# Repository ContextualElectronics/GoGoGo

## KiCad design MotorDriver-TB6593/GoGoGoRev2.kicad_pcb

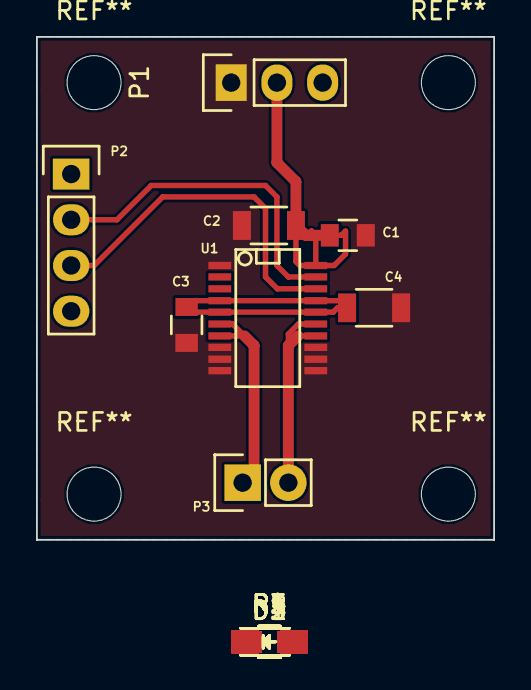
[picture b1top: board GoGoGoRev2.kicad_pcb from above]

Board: 2 copper layers, 25.4 x 27.9 mm, 17 parts (0 on the bottom side), 13 nets.

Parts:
C1, C3: .1U; C_0805
C2, C4: 10U; C_1206
D1, D2, D3, D4: LED; LED-0805
P1: CONN_01X03; Pin_Header_Straight_1x03
P2: CONN_01X04; Pin_Header_Straight_1x04
P3: CONN_01X02; Pin_Header_Straight_1x02
R1, R2, R3, R4: 1K; R_0805_HandSoldering
R5: 0; R_0805_HandSoldering
U1: TB6593FNG; SSOP-20

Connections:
/IN1: D3.2, P2.3, U1.18
/IN2: D4.2, P2.2, U1.19
/O1: P3.1, U1.6, U1.7
/O2: P3.2, U1.14, U1.15
/PWM: P2.1, U1.2
/STBY: P2.4, U1.3
/VCC: C1.1, C2.1, P1.2, R5.2, U1.20
/VM: C3.1, C4.1, D1.2, D2.2, P1.3, R5.1, U1.4, U1.5, U1.16, U1.17
GND: C1.2, C2.2, C3.2, C4.2, P1.1, R1.1, R2.1, R3.1, R4.1, U1.1, U1.8, U1.9, U1.10, U1.11, U1.12, U1.13
unnamed: D1.1, R1.2
unnamed: D2.1, R2.2
unnamed: D3.1, R3.2
unnamed: D4.1, R4.2

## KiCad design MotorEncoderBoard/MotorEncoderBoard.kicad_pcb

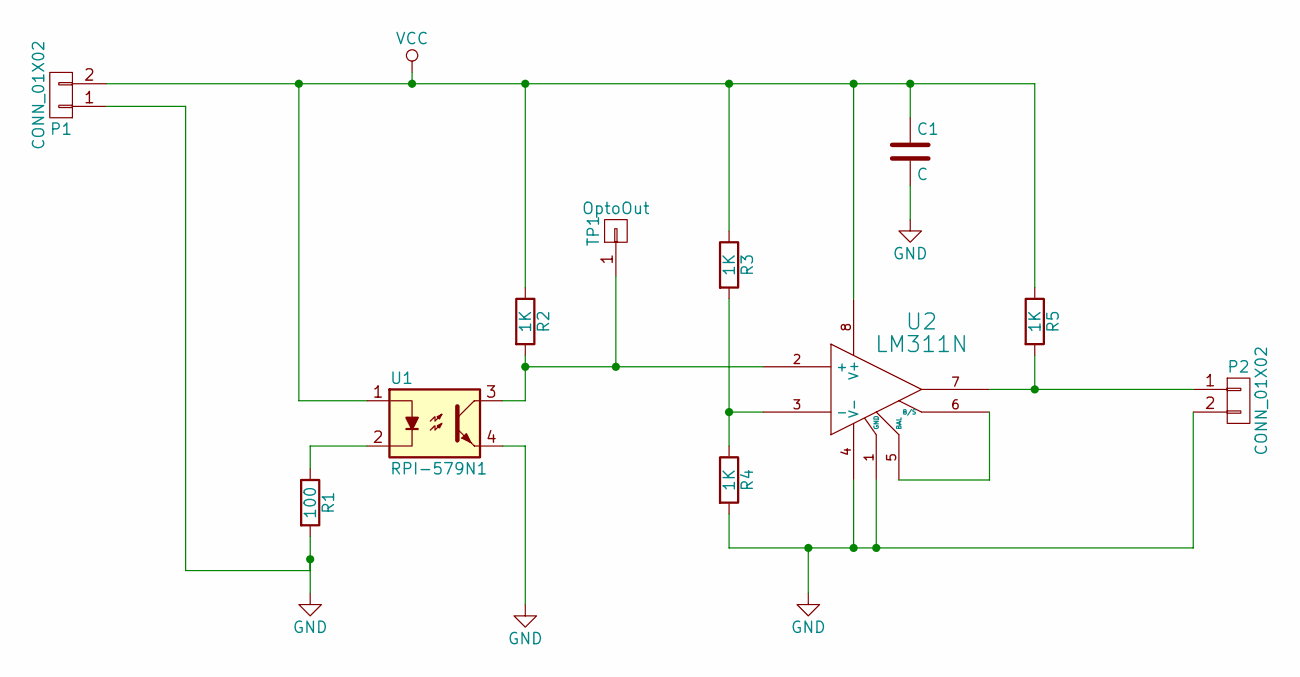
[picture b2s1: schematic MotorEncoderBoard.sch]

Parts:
C1: C; C_0805_HandSoldering
P1, P2: CONN_01X02; Pin_Header_Straight_1x02
R1: 100; R_0805_HandSoldering
R2, R3, R4, R5: 1K; R_0805_HandSoldering
TP1: OptoOut; Measurement_Point_Round-SMD-Pad_Big
U1: RPI-579N1
U2: LM311N; SOIC-8_3.9x4.9mm_Pitch1.27mm

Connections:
GND: C1.2, P1.1, P2.2, R1.2, R4.2, U1.4, U2.1 (GND), U2.4 (V-)
unnamed: P2.1, R5.2, U2.7
unnamed: R1.1, U1.2
unnamed: R2.2, TP1.1, U1.3, U2.2 (+)
unnamed: R3.2, R4.1, U2.3 (-)
unnamed: U2.5 (BAL), U2.6 (B/S)
VCC: C1.1, P1.2, R2.1, R3.1, R5.1, U1.1, U2.8 (V+)

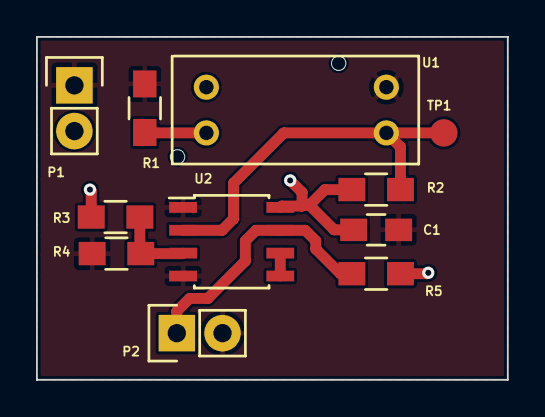
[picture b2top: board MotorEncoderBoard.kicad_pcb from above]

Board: 2 copper layers, 26.2 x 19.0 mm, 11 parts (0 on the bottom side), 7 nets.

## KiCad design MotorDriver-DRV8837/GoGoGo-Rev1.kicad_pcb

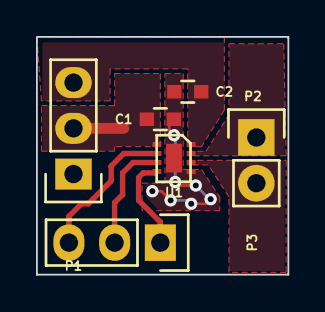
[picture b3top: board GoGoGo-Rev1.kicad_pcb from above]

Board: 2 copper layers, 14.0 x 13.2 mm, 6 parts (0 on the bottom side), 8 nets.

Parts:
C1, C2: C; C_0603
P1, P3: CONN_01X03; Pin_Header_Straight_1x03
P2: CONN_01X02; Pin_Header_Straight_1x02
U1: DRV8837DSGR; PWSON-N8

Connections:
/IN1: P3.2, U1.6
/IN2: P3.1, U1.5
/OUT1: P2.1, U1.2
/OUT2: P2.2, U1.3
/VIN: C1.1, P1.2, U1.8
/VM: C2.1, P1.3, U1.1
/nSleep: P3.3, U1.7
GND: C1.2, C2.2, P1.1, U1.4

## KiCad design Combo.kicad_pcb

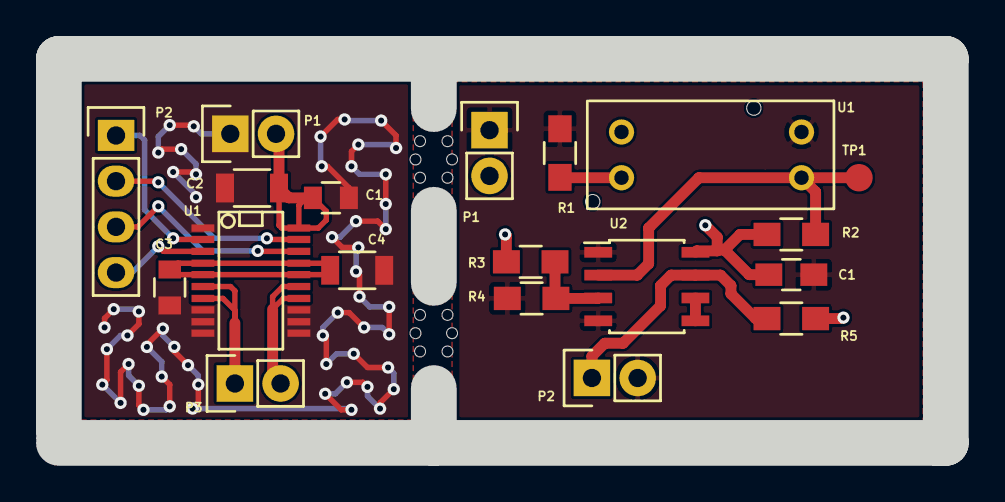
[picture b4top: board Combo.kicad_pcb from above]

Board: 2 copper layers, 49.3 x 21.3 mm, 19 parts (0 on the bottom side), 15 nets.

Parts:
C1: C; C_0805_HandSoldering
C1#2, C3: .1U; C_0805
C2, C4: 10U; C_1206
P1, P1#2, P2, P3: CONN_01X02; Pin_Header_Straight_1x02
P2#2: CONN_01X04; Pin_Header_Straight_1x04
R1: 100; R_0805_HandSoldering
R2, R3, R4, R5: 1K; R_0805_HandSoldering
TP1: OptoOut; Measurement_Point_Round-SMD-Pad_Small
U1: RPI-579N1
U1#2: TB6593FNG; SSOP-20
U2: LM311N; SOIC-8_3.9x4.9mm_Pitch1.27mm

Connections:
/IN1: P2#2.3, U1#2.18
/IN2: P2#2.2, U1#2.19
/O1: P3.1, U1#2.6, U1#2.7
/O2: P3.2, U1#2.14, U1#2.15
/PWM: P2#2.1, U1#2.2
/STBY: P2#2.4, U1#2.3
/VCC: C1#2.1, C2.1, P1#2.2, U1#2.20
/VM: C3.1, C4.1, U1#2.4, U1#2.5, U1#2.16, U1#2.17
GND: C1.2, C1#2.2, C2.2, C3.2, C4.2, P1.1, P1#2.1, P2.2, R1.2, R4.2, U1.4, U1#2.1, U1#2.8, U1#2.9, U1#2.10, U1#2.11, U1#2.12, U1#2.13, U2.1, U2.4
unnamed: P2.1, R5.2, U2.7
unnamed: R1.1, U1.2
unnamed: R2.2, TP1.1, U1.3, U2.2
unnamed: R3.2, R4.1, U2.3
unnamed: U2.5, U2.6
VCC: C1.1, P1.2, R2.1, R3.1, R5.1, U1.1, U2.8

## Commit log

2015-06-13 init schematic
2015-06-13 Finished simple schematic, added netlists
2015-06-13 Added PWSON footprint
2015-06-13 PCB finished
2015-06-14 Moved into Rev1 subdirectory
2015-06-14 Added Rev2 Schematic
2015-06-14 Added TB6593 to schematic
2015-06-14 Added netlist and assigned footprints
2015-06-14 Finished layout
2015-06-14 Missed one change on layout
2015-06-14 Added motorencoderboard schematic to project
2015-06-14 Finished schematic
2015-06-15 Initial Layout
2015-06-15 Finished PCB and generated Gerbers
2015-06-15 Added sketchup model and datasheet
2015-06-15 Updated fill zones to get better copper coverage
2015-06-17 Added motor encoder disk KiCad files
2015-06-23 Changed board outline layer to conform to OSHPark rules
2015-06-26 Combined two boards into a single file with snap off board edge tabs
2015-06-28 Added gerbers to top level folder
2015-07-12 updated part numbers
2015-07-12 Updated schematic with MPNs and Links
2015-08-03 Arduino code for testing the motor driver board (rev 2)
2015-10-04 Renamed driver boards for better tracking
2015-10-04 Replaced parts, started redoing layout
2015-10-05 Finished layout, still need via stitching and DRC/DFM checks
2015-10-05 Renamed files to match directory
2015-10-05 Added via footprint and stitched the planes together.
2015-10-05 Did DRC and added silkscreen
2015-10-05 Added previous commit # for tracking PCBs
2015-10-06 Added another set of Arduino test code
2015-10-19 Staged files for OSHPark upload
2015-12-06 Updated motor test to work with the new GoGoGo Motor Driver Rev 2 board
2016-03-29 Updated code to control wheel by number of steps
2016-03-29 Created a function to simplify the main loop
2016-06-29 Working Left Wheel conversion from Arduino code
2016-08-31 Wrapped up left wheel, adjusted pins to have both motor drivers attached
2016-08-31 Added a stop and start button press
2016-09-27 A refactoring pass to move code out of main
2016-09-29 Added in Ceedling TDD project for our code
2016-10-01 Should not have added build output from TDDing
2016-10-01 Correctly ignore all contents of the build directory except placeholder file
2016-11-01 Added more unit tests for our while loop and flags
2016-11-28 Removed the step count & while loop
2016-12-29 Starting on new DriveTrain module
2016-12-29 Rudimentary support for turning, direction and velocity
2016-12-30 Wheel integration testing code
